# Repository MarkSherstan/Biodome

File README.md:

# Biodome
Hardware, firmware, and Bluetooth Low Energy (BLE) iOS app for monitoring plants around the house. Inspired by the Cloud Forest in Singapore.

# Requirements
## App
* Computer running macOS
* Xcode 13.0 or greater
* Device running iOS 15.0 or greater (UI built for iPhone Xs)

## Hardware
* Raspberry Pi 3B+
* Custom PCB board (boards are built with KiCad 5 and manufactured by JLCPCB))

## Firmware
* Python 3 
* Standard Raspbian OS

# Setup
## App
* Build using Xcode and upload to iOS device. See `/Resources` for example screenshots of the app using simulated data.

## Hardware
* Power on system (remember RPi is 3V3 logic)

## Firmware
As of BlueZ version 5.43 (currently shipped with Raspbian), some BLE aspects are still experimental. You will need to add the 'Experimental' flag to the bluetooth daemon. Open the file: `sudo nano /etc/systemd/system/dbus-org.bluez.service` and add the `-E` flag at the end of the `ExecStart` line. It should look like this:
```
ExecStart=/usr/lib/bluetooth/bluetoothd -E
```
To disable auto battery reading and prevent connection issues, edit the same file and add `-P battery` to the end of the `ExecStart` line to disable the Battery feature in bluetooth. Your ExecStart should look something like:
```
ExecStart=/usr/lib/bluetooth/bluetoothd -E -P battery
```
Run `systemctl daemon-reload` and `systemctl restart bluetooth` to apply the changes to the Bluetooth service

Navigate to `\Firmware` and run `python3 main.py`. The RPi is now ready to share values with the iOS app.

# Future Work
## App
* Fix connection logic
* Connect to multiple devices
* More general UI layout

### Resources 
Core Bluetooth
* https://www.raywenderlich.com/231-core-bluetooth-tutorial-for-ios-heart-rate-monitor#toc-anchor-009
* https://www.novelbits.io/intro-ble-mobile-development-ios-part-2/
* https://learn.adafruit.com/build-a-bluetooth-app-using-swift-5/code
* https://punchthrough.com/core-bluetooth-basics/

Style and UI:
*  https://betterprogramming.pub/flat-design-list-swiftui-part-i-ab9e841720cd
*  https://developer.apple.com/tutorials/swiftui/building-lists-and-navigation
*  https://betterprogramming.pub/creating-an-apple-like-splash-screen-in-swiftui-fdeb36b47e81

Other:
* https://www.raywenderlich.com/2164-arduino-tutorial-integrating-bluetooth-le-and-ios-with-swift#toc-anchor-009

## Hardware
* Use digital pin to wake up moisture sensor (change to 3.3V 555 timer)
* Check backorder on BME280 - Not currently used for V1
* Make the board act as a shield for the Pi (pins and mounting holes)

## Firmware 
* Website JavaScript interface (similar to Octo-Print)
* Slow logging... Log on ram for 24h then save to SD card (Dont burn out SD card)
* Photos/Image Processing, moisture, humidity, temperature, light, pressure

# Node Install Instructions (RPi)
sudo apt-get update
sudo apt-get dist-upgrade

curl -sL https://deb.nodesource.com/setup_14.x | sudo -E bash -
sudo apt-get install -y nodejs
node -v

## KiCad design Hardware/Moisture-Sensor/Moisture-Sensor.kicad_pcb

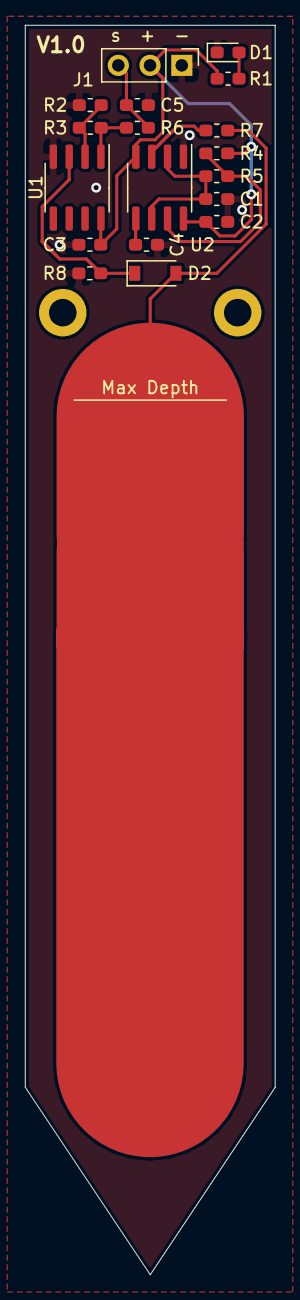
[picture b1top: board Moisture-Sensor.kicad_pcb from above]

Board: 2 copper layers, 20.0 x 100.0 mm, 20 parts (0 on the bottom side), 12 nets.

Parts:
C1: 470 pF; C_0603_1608Metric_Pad1.05x0.95mm_HandSolder
C2, C3: 0.1 uF; C_0603_1608Metric_Pad1.05x0.95mm_HandSolder
C4: 10 nF; C_0603_1608Metric_Pad1.05x0.95mm_HandSolder
C5: 4.7 uF; C_0603_1608Metric_Pad1.05x0.95mm_HandSolder
D1: Green 2.2V 20mA; LED_0603_1608Metric_Pad1.05x0.95mm_HandSolder
D2: 4148; D_SOD-123
H1, H2: M2; MountingHole_2.2mm_M2_ISO14580_Pad
J1: Input; PinHeader_1x03_P2.54mm_Vertical
R1: 150 ohm; R_0603_1608Metric_Pad1.05x0.95mm_HandSolder
R2: DNP; R_0603_1608Metric_Pad1.05x0.95mm_HandSolder
R3: 0 ohm; R_0603_1608Metric_Pad1.05x0.95mm_HandSolder
R4: 1.5 kohm; R_0603_1608Metric_Pad1.05x0.95mm_HandSolder
R5: 2.4 kohm; R_0603_1608Metric_Pad1.05x0.95mm_HandSolder
R6: 100 ohm; R_0603_1608Metric_Pad1.05x0.95mm_HandSolder
R7: 10 kohm; R_0603_1608Metric_Pad1.05x0.95mm_HandSolder
R8: 1 Mohm; R_0603_1608Metric_Pad1.05x0.95mm_HandSolder
U1: LMV358; SOIC-8_3.9x4.9mm_P1.27mm
U2: NE555; SOIC-8_3.9x4.9mm_P1.27mm

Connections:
+5V: C2.2, C3.2, J1.2, R1.1, R4.1, U1.8, U2.4, U2.8
GND: C1.1, C2.1, C3.1, C4.1, C5.1, D1.1, J1.1, R2.1, R8.2, U1.4, U2.1
unnamed: C1.2, R5.2, U2.2, U2.6
unnamed: C4.2, U2.5
unnamed: D1.2, R1.2
unnamed: D2.1, R8.1, U1.3
unnamed: D2.2, R7.2
unnamed: R2.2, R3.1, U1.2
unnamed: R3.2, R6.1, U1.1
unnamed: R4.2, R5.1, U2.7
unnamed: R7.1, U2.3
Sig: C5.2, J1.3, R6.2

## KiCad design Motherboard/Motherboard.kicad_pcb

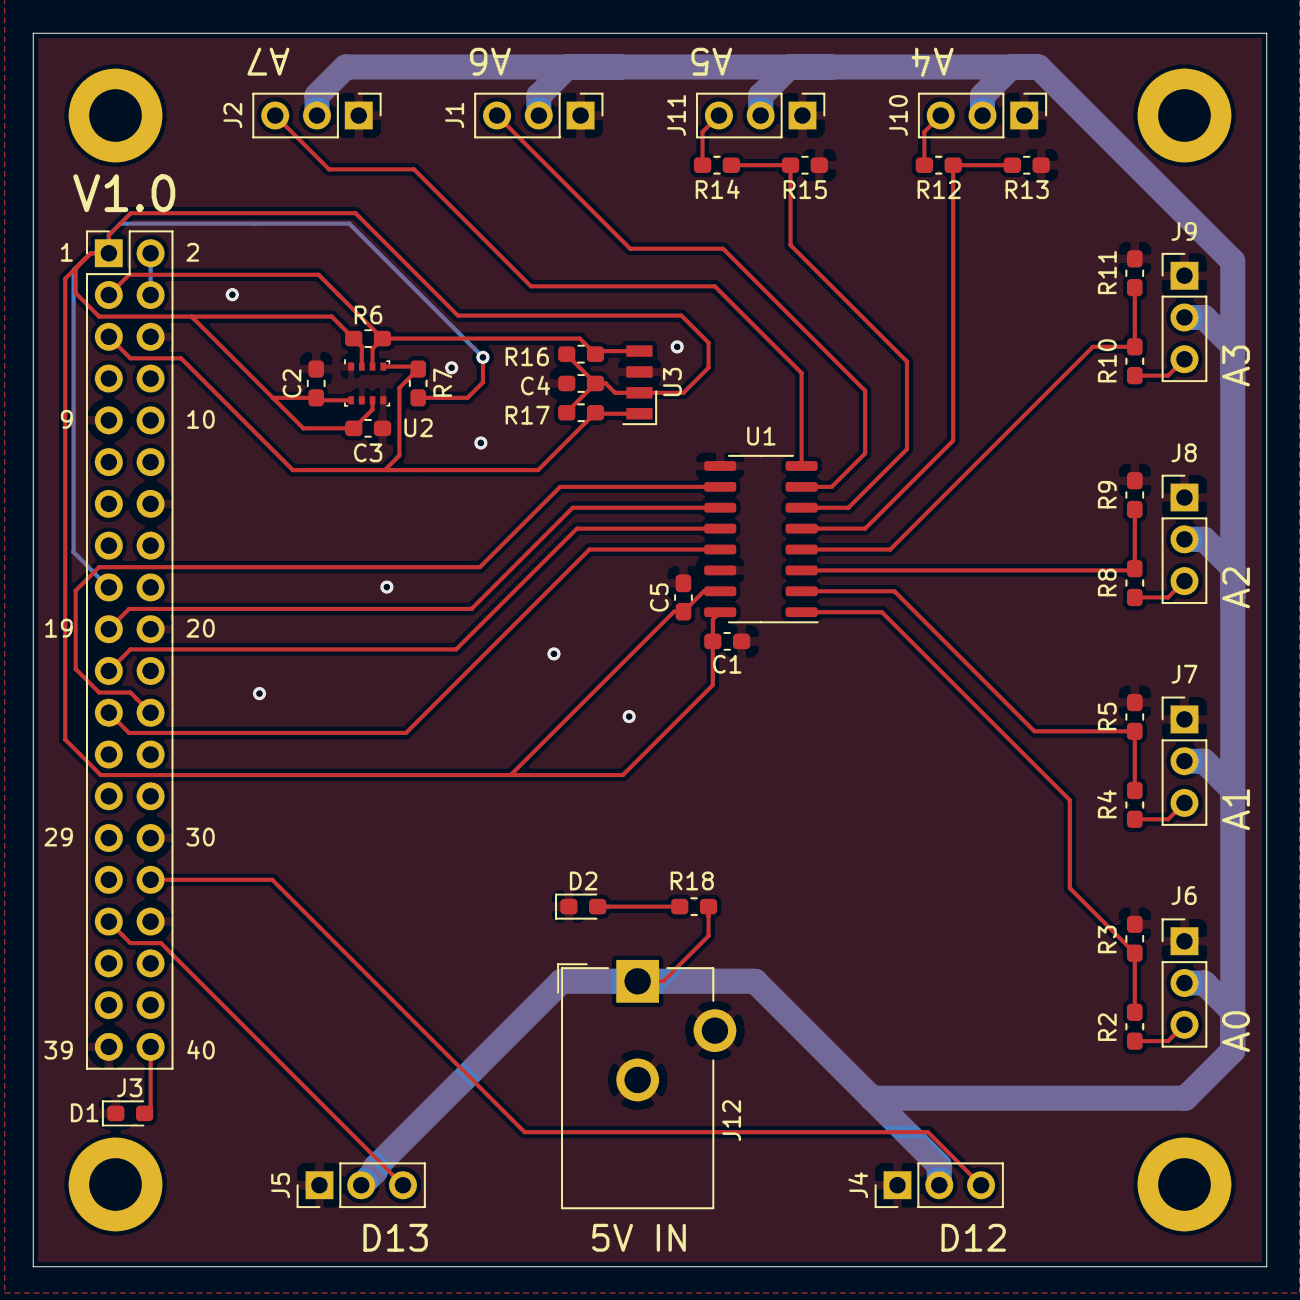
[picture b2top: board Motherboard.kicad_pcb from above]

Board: 2 copper layers, 75.0 x 75.0 mm, 43 parts (0 on the bottom side), 28 nets.

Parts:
C1: 1 uF; C_0603_1608Metric_Pad1.05x0.95mm_HandSolder
C2, C3, C4: 0.1 uF; C_0603_1608Metric_Pad1.05x0.95mm_HandSolder
C5: 1 uF; C_0603_1608Metric_Pad1.08x0.95mm_HandSolder
D1: Blue 3.3V 20mA; LED_0603_1608Metric_Pad1.05x0.95mm_HandSolder
D2: Green 2.2V 20mA; LED_0603_1608Metric_Pad1.05x0.95mm_HandSolder
H1, H2, H3, H4: M3; MountingHole_3.2mm_M3_ISO7380_Pad
J1: AUX Analog A; PinHeader_1x03_P2.54mm_Vertical
J2: AUX Analog B; PinHeader_1x03_P2.54mm_Vertical
J3: RPi 3B+; PinHeader_2x20_P2.54mm_Vertical
J4: AUX Digital A; PinHeader_1x03_P2.54mm_Vertical
J5: AUX Digital B; PinHeader_1x03_P2.54mm_Vertical
J6: Moisture 0; PinHeader_1x03_P2.54mm_Vertical
J7: Moisture 1; PinHeader_1x03_P2.54mm_Vertical
J8: Moisture 2; PinHeader_1x03_P2.54mm_Vertical
J9: Moisture 3; PinHeader_1x03_P2.54mm_Vertical
J10: Moisture 4; PinHeader_1x03_P2.54mm_Vertical
J11: Moisture 5; PinHeader_1x03_P2.54mm_Vertical
J12: Power In; BarrelJack_CUI_PJ-102AH_Horizontal
R2, R4, R8, R10, R12, R14: 1.7 kohm; R_0603_1608Metric_Pad1.05x0.95mm_HandSolder
R3, R5, R9, R11, R13, R15: 3.3 kohm; R_0603_1608Metric_Pad1.05x0.95mm_HandSolder
R6, R7, R16, R17: 4.7 kohm; R_0603_1608Metric_Pad1.05x0.95mm_HandSolder
R18: 150 ohm; R_0603_1608Metric_Pad1.05x0.95mm_HandSolder
U1: MCP3008; SOIC-16_3.9x9.9mm_P1.27mm
U2: BME280; Bosch_LGA-8_2.5x2.5mm_P0.65mm_ClockwisePinNumbering
U3: VEML7700

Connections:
+3V3: C1.2, C2.1, C3.1, C4.1, C5.1, J3.1, J3.17, R6.2, R7.2, R16.2, R17.2, U1.15, U1.16, U2.2, U2.6, U2.8, U3.2
+5V: J1.2, J2.2, J4.2, J5.2, J6.2, J7.2, J8.2, J9.2, J10.2, J11.2, J12.1, R18.1
+5VA: J3.2, J3.4
A0: R2.2, R3.1, U1.1
A1: R4.2, R5.1, U1.2
A2: R8.2, R9.1, U1.3
A3: R10.2, R11.1, U1.4
A4: R12.2, R13.1, U1.5
A5: R14.2, R15.1, U1.6
A6: J1.3, U1.7
A7: J2.3, U1.8
D12: J3.32, J4.3
D13: J3.33, J5.3
GND: C1.1, C2.2, C3.2, C4.2, C5.2, D1.1, D2.1, J1.1, J2.1, J3.6, J3.9, J3.14, J3.20, J3.25, J3.30, J3.34, J3.39, J4.1, J5.1, J6.1, J7.1, J8.1, J9.1, J10.1, J11.1, J12.2, J12.3, R3.2, R5.2, R9.2, R11.2, R13.2, R15.2, U1.9, U1.14, U2.1, U2.5, U2.7, U3.3
GPIO_2-SDA: J3.3, R6.1, R16.1, U2.3, U3.4
GPIO_3-SCL: J3.5, R7.1, R17.1, U2.4, U3.1
GPIO_8-CE0: J3.24, U1.10
GPIO_9-MISO: J3.21, U1.12
GPIO_10-MOSI: J3.19, U1.11
GPIO_11-SCLK: J3.23, U1.13
GPIO_21: D1.2, J3.40
unnamed: D2.2, R18.2
unnamed: J6.3, R2.1
unnamed: J7.3, R4.1
unnamed: J8.3, R8.1
unnamed: J9.3, R10.1
unnamed: J10.3, R12.1
unnamed: J11.3, R14.1

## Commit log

2020-12-27 Jot down a few ideas for scope of project.
2020-12-27 Selected MCP3008 for ADC and started RPi pinout
2020-12-27 Selected most of the required components
2020-12-28 Labeled RPi GPIO pin and MCP3008. Need 5v external
2020-12-28 BME280
2020-12-28 555 timer complete
2020-12-28 Op amp is updated
2020-12-28 Schematic just needs a double check
2020-12-28 started layout
2020-12-28 Need to find an ambient light sensor
2020-12-28 Schematic reviewed
2020-12-28 half layed out, switch to other computer
2020-12-28 Almost done routing, need to move bypass caps
2020-12-28 Layout looks good and passed DRC
2020-12-28 Create gerbers
2020-12-28 schematic looks mostly routed, need to finalize components
2020-12-29 Schematic mostly done, just need to double check
2020-12-29 Quick layout before schematic review
2020-12-30 Schematic is fully reviewed
2020-12-30 added missing footprint on new cap
2020-12-30 Analog routed
2020-12-30 Routing complete
2020-12-30 generate gerbers
2020-12-30 add silk screen
2020-12-30 Add gerbers
2020-12-30 Add PDF schematics
2021-01-01 Re commit gerbers
2021-01-01 Add BOM
2021-04-23 Update to use adafruit lib
2021-09-11 Initial commit of Swift files and a very basic UI that is 50% complete.
2021-09-11 Increase symbol size and add sensor fields.
2021-09-12 Create BLEManager class and link too a landing scanning page
2021-09-12 Link bluetooth scan view with sensor output view
2021-09-12 Pass selected data between UI's
2021-09-12 Clean up unused functions and prepare for scanning toggle
2021-09-12 Add connection buttons and rough link to BLEclass
2021-09-12 Add CBPeripheral to struct and set up state/observed/environment objects.
2021-09-12 Validate connection to heart rate monitor
2021-09-12 Add disconnect backend
2021-09-12 Slotting in pre baked heart rate code (https://www.raywenderlich.com/231-core-bluetooth-tutorial-for-ios-heart-rate-monitor#toc-anchor-009)
2021-09-13 Update resource list
2021-09-14 Use LightBlue to simulate data and move variables directly into the UI with @Published
2021-09-15 Space out and clean up the UI, make the sensor entry a nice usable class
2021-09-15 Add connection state and test on updated iPhone Xs (14.8)
2021-09-19 Add RPi setup quick notes
2021-09-19 Fix issue where preview was not appearing in Content View
2021-09-19 Prep for toggle switch and change list to be more general with a struct view and header.
2021-09-22 Update for Xcode 13 and iOS 15
2021-09-22 Add toggle switch for scanning in place of 2x push buttons. Scan for all devices and filter by name incase UUID is not advertised.
2021-09-22 Clear list whenever rescanning and fix constraint warning messages with declaring .navigationViewStyle
2021-09-23 Create hardware directory
2021-09-23 Commit GATT server base files
2021-10-02 Add python cache gitignore
2021-10-02 Properly link directories
2021-10-02 Send CPU temp in a more effcient manner.
2021-10-02 Remove onHeartRateReceived, discover all services, and bit shift temperature readings.
2021-10-02 Empty the playground.
2021-10-03 Switch from List to Grid
2021-10-03 Add some color
2021-10-03 Pass color arguments more efficiently and update build to iOS 15
2021-10-03 Add notes to playground and change color scheme
2021-10-03 Adjust alpha view to look more like calendar, round values, add border.
2021-10-03 Fix rounding on UI and test sheet view
2021-10-04 Fix spacing for iPhone Xs
2021-10-04 Prep for moving scan view into sheet view
2021-10-05 Upgrade to sheet view
2021-10-05 Add loading spinner for search list.
2021-10-06 Add interaction where connected device is separated list -> Need to add connection logic still.
2021-10-06 Have progress view when selecting a device.
2021-10-06 Add UUID, fail to connect manager, and deal with connection and search list transitions.
2021-10-06 Remove progress wheel and just put everything in connection list with status. Commented out log noise of connection messages and characteristics.
2021-10-06 Add sheet view as its own file (delete scan view). Remove disconnecting scan state.
2021-10-06 Add environmental object to render canvas preview.
2021-10-07 Fix the multi array logic (and connection/searching lists) basing it on the bluetooth UUID.
2021-10-07 Put dashes when there is no connected device on UI values.
2021-10-09 Add navigation based on button press and start configuring the info view.
2021-10-09 Add navigation bar titles and deal with logic of disconnecting and updating lists.
2021-10-09 Fix bug where sometimes device name went on 2 lines.
2021-10-09 Info view can preview again with a quick if statement
2021-10-09 Add rough app icon (required restart for Xcode 13 and iOS 15 to show).
2021-10-10 Update app icon and include source file.
2021-11-14 Update README To Do
2021-12-08 Fix bit shift data type and delete some print statements
2021-12-09 Tidy up some minor logic
2021-12-09 formatting
2021-12-09 Tidy up
2021-12-09 Add parameter structure to sensor widgets and started commenting code
2021-12-09 Finish commenting views
2021-12-10 remove temp files
2021-12-10 Update file paths
2021-12-10 Rename peripheral related variables for clarity.
2021-12-10 Add comments
2021-12-11 Remove unit characteristic
2021-12-11 Remove temp descriptor
2021-12-11 Update variable names
2021-12-11 Add a master UUID
2021-12-11 Serive made up of characeristics
2021-12-11 Remove unused lines
2021-12-11 Update UUID service and characteristics
2021-12-11 Remove name check as we have the UUID advertised
2021-12-11 Update the two temperature values independently
2021-12-11 Update UUIDs and inits
2021-12-11 Send random data
2021-12-13 Make generic
2021-12-13 Update file names
2021-12-13 Split up BLE and main
2021-12-13 Add sensor class for a data stream
2021-12-13 Add moisture and light services
2021-12-13 Add moisture and light characteristics
2021-12-13 Create moisture and light sensor classes
2021-12-13 Remove src (replaced with Firmware)
2021-12-13 Add resource images
2021-12-13 Fix image
2021-12-13 Node install instructions
2021-12-13 Add stylesheet
2021-12-14 Update port to 8000
2021-12-14 Remove comments
2022-06-19 Initial commit pubsub example
2022-06-19 Simplify publish
2022-06-19 Add Pods
2022-06-19 Only need AWSIoT
